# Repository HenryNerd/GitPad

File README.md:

# GitPad
A Macro Pad for using git to mange your code

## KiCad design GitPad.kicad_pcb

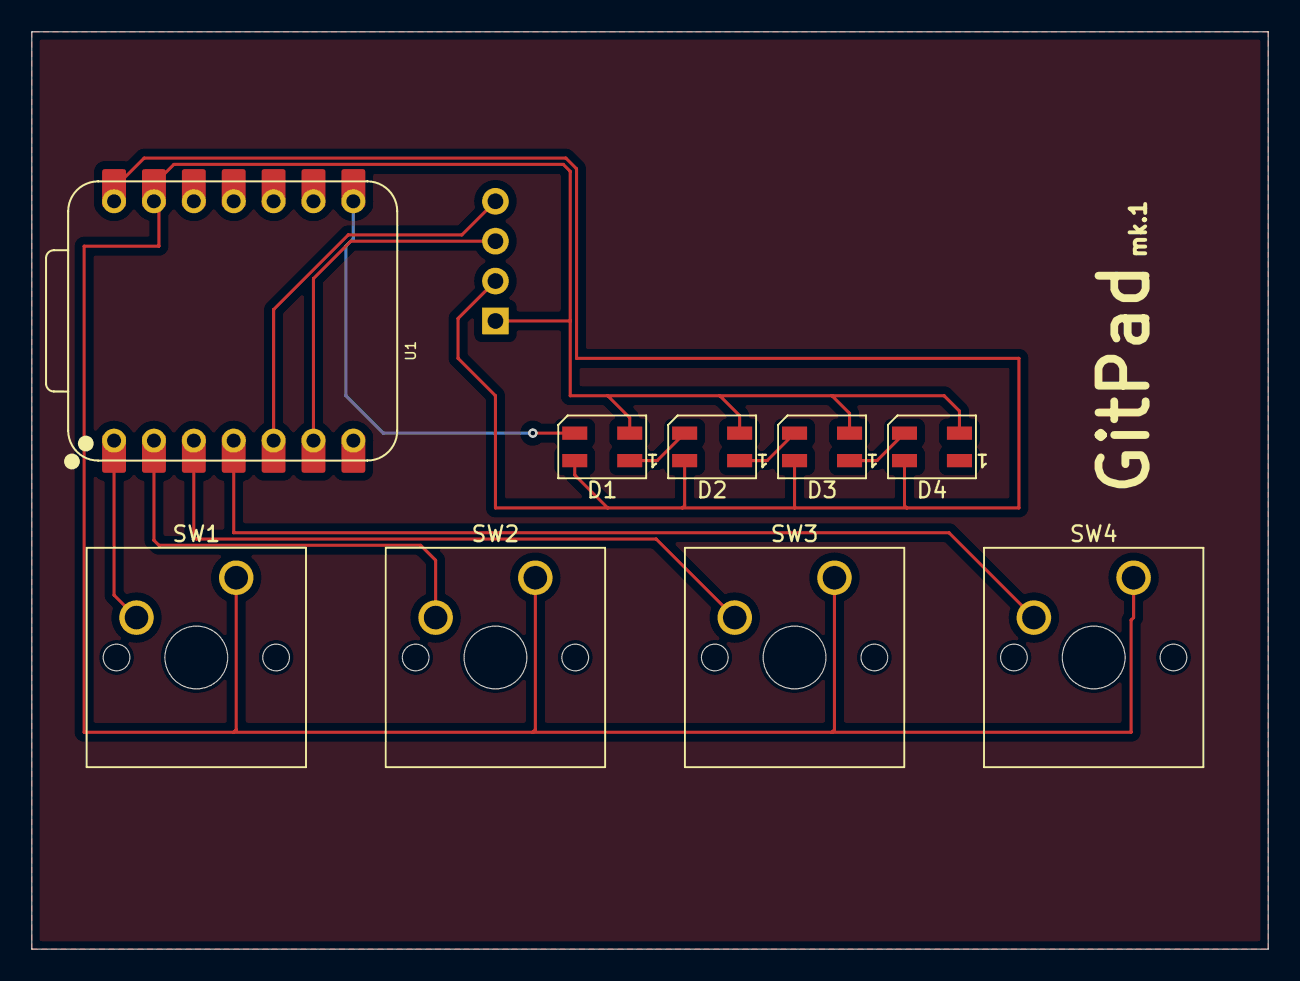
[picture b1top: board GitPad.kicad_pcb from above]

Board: 2 copper layers, 78.7 x 58.4 mm, 10 parts (0 on the bottom side), 12 nets.

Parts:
D1, D2, D3, D4: SK6812MINI; LED_SK6812MINI_PLCC4_3.5x3.5mm_P1.75mm
J1: OLED_128x32
SW1, SW2, SW3, SW4: SW_Push; SW_Cherry_MX_1.00u_PCB
U1: XIAO-RP2040-DIP

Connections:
+5V: D1.4 (VDD), D2.4 (VDD), D3.4 (VDD), D4.4 (VDD), J1.2 (VCC), U1.14 (VBUS)
GND: D1.2 (VSS), D2.2 (VSS), D3.2 (VSS), D4.2 (VSS), J1.1 (GND), SW1.1, SW2.1, SW3.1, SW4.1, U1.13 (GND)
unnamed: D1.3 (DIN), U1.8 (GPIO1/RX)
unnamed: D1.1 (DOUT), D2.3 (DIN)
unnamed: D2.1 (DOUT), D3.3 (DIN)
unnamed: D3.1 (DOUT), D4.3 (DIN)
unnamed: SW1.2, U1.1 (GPIO26/ADC0/A0)
unnamed: SW2.2, U1.2 (GPIO27/ADC1/A1)
unnamed: SW3.2, U1.3 (GPIO28/ADC2/A2)
unnamed: SW4.2, U1.4 (GPIO29/ADC3/A3)
SCL: J1.3 (SCL), U1.6 (GPIO7/SCL)
SDA: J1.4 (SDA), U1.5 (GPIO6/SDA)

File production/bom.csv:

Designator,Footprint,Quantity,Value,LCSC Part #
"D1, D2, D3, D4",LED_SK6812MINI_PLCC4_3.5x3.5mm_P1.75mm,4,SK6812MINI,
J1,OLED_128x32,1,OLED_128x32,
"SW1, SW2, SW3, SW4",SW_Cherry_MX_1.00u_PCB,4,SW_Push,
U1,XIAO-RP2040-DIP,1,XIAO-RP2040-DIP,

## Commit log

2025-05-17 Setup Kicad & Add Journal.md
2025-05-17 Update Schematic
2025-05-18 Update PCB
2025-05-24 Add Case Base STEP File
